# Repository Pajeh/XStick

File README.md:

XStick
======

compact breadboard-friendly XMO XS1-L4 board with USB-UART and all GPIO exposed
.
The board was designed with the freeware version of eagle and the modified design rules of Seeed Studio.
#ToDo list
* solder and test 
* Add at least 2 LEDs on board (soon)

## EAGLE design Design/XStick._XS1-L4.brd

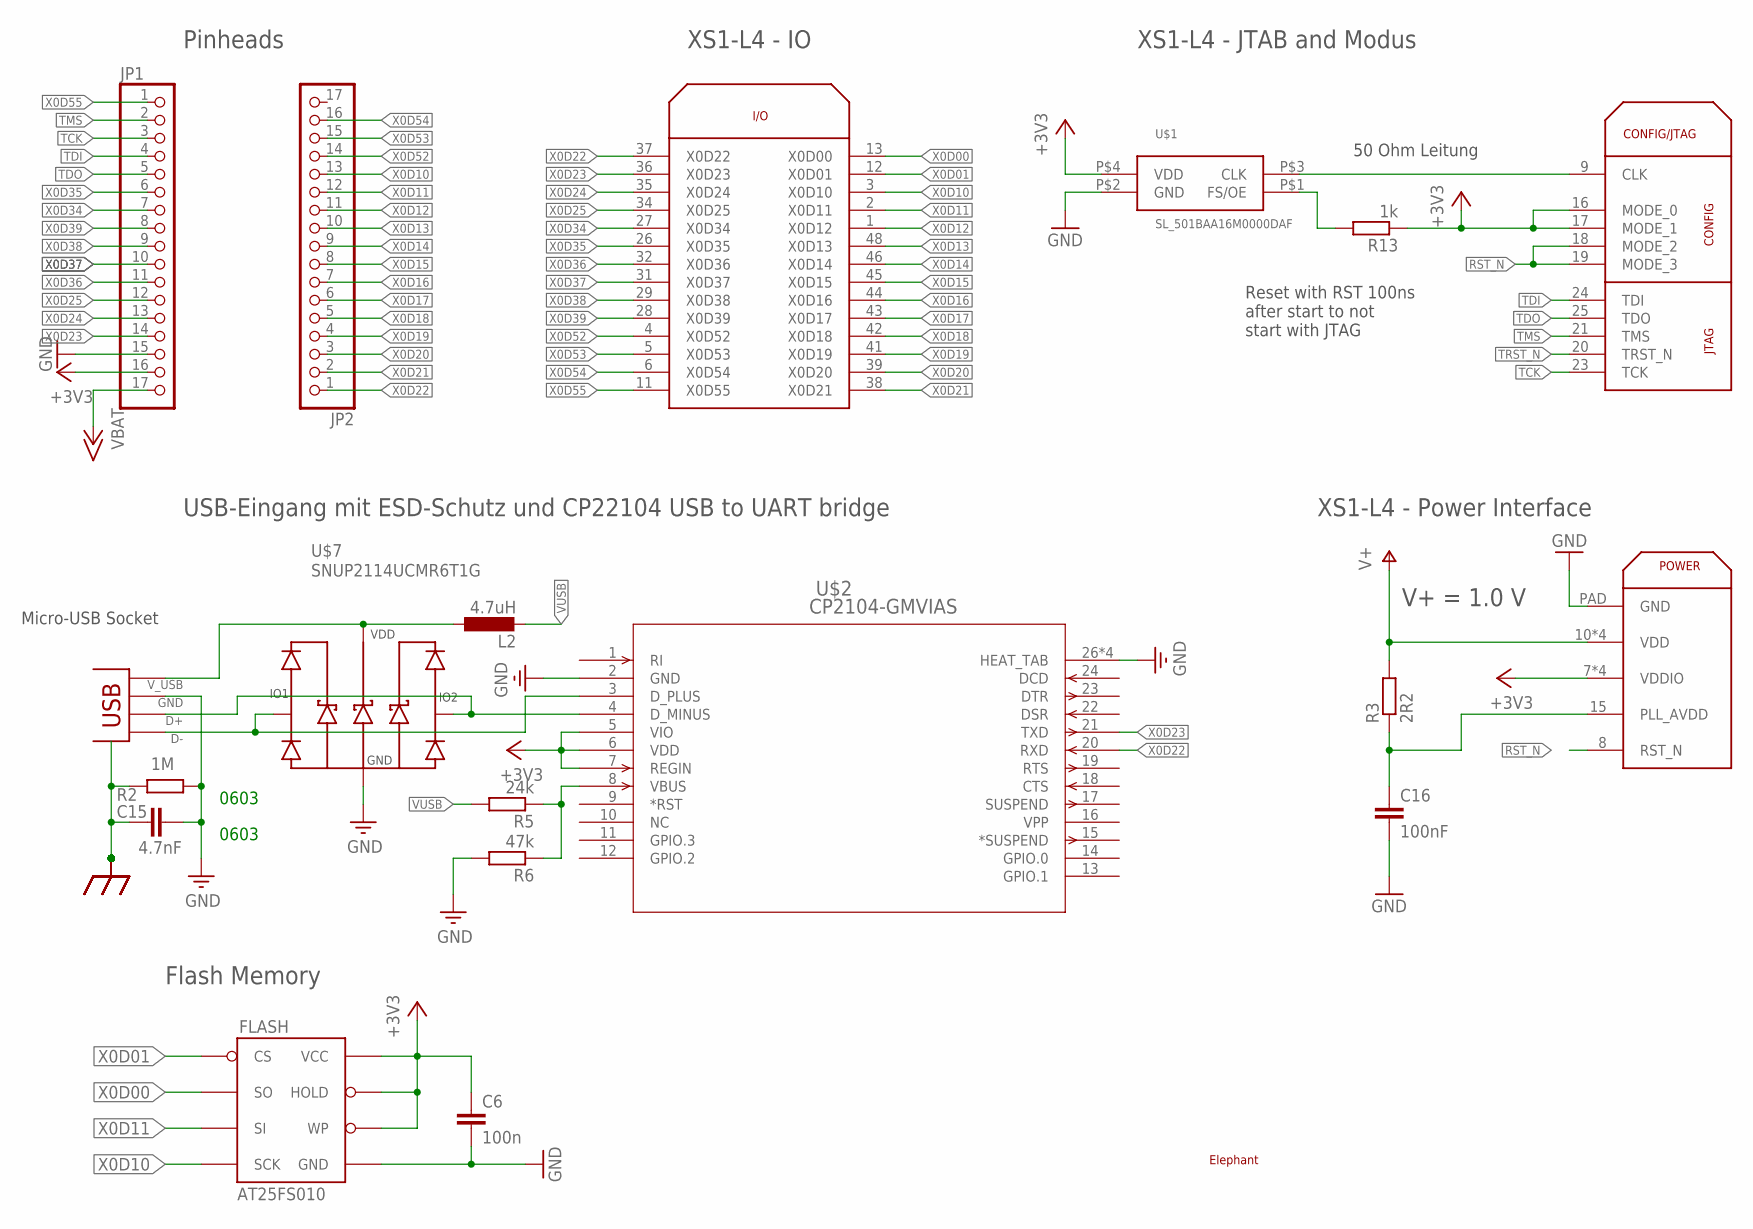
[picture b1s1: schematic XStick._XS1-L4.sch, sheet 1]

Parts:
C6: 100n; C0402
C15: 4.7nF; C0603M
C16: 100nF; C0402
FLASH: AT25FS010; SO08WIDE
JP1, JP2: PINHD-1X17; 1X17
L2: 4.7uH; C0603
R2: 1M; R0603M
R3: 2R2; R0603
R5: 24k; R0603
R6: 47k; R0603
R13: 1k; R0603
U$1: SL_501BAA16M0000DAF; SL_OSZ
U$2: CP2104-GMVIAS; QFN24_4X4_VIAS
U$4: ELEPHANT
U$5: XS1-L01A-TQ48; TQFP48
U$7: SNUP2114UCMR6T1G; TSOP-6
USB_SKT: USB_SHIELD_8; USB_MICRO_B

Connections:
+3V3: C6.1, FLASH.3 (WP), FLASH.7 (HOLD), FLASH.8 (VCC), JP1.16, R13.1, U$1.P$4 (VDD), U$2.5 (VIO), U$2.6 (VDD), U$2.7 (REGIN), U$5.7 (VDDIO), U$5.14 (VDDIO), U$5.16 (MODE_0), U$5.17 (MODE_1), U$5.30 (VDDIO), U$5.40 (VDDIO); also elsewhere on the board
+15V: JP1.17; also elsewhere on the board
D+: U$2.4 (D_MINUS), U$7.1 (I/O1), USB_SKT.D+
D-: U$2.3 (D_PLUS), U$7.6 (I/O2), USB_SKT.D-
GND: C6.2, C15.1, C16.2, FLASH.4 (GND), JP1.15, R2.2, R6.2, U$1.P$2 (GND), U$2.2 (GND), U$2.26 (HEAT_TAB), U$2.27 (HEAT_TAB), U$2.28 (HEAT_TAB), U$2.29 (HEAT_TAB), U$5.PAD (GND), U$7.2 (VN), USB_SKT.GND; also elsewhere on the board
unnamed: U$1.P$3 (CLK), U$5.9 (CLK)
unnamed: L2.1, U$7.5 (VP), USB_SKT.VBUS (V_USB)
unnamed: R13.2, U$1.P$1 (FS/OE)
unnamed: R5.1, R6.1, U$2.8 (VBUS)
unnamed: C16.1, R3.1, U$5.15 (PLL_AVDD)
RST_N: U$5.8 (RST_N), U$5.18 (MODE_2), U$5.19 (MODE_3); also elsewhere on the board
TCK: JP1.3, U$5.23 (TCK)
TDI: JP1.4, U$5.24 (TDI)
TDO: JP1.5, U$5.25 (TDO)
TMS: JP1.2, U$5.21 (TMS)
TRST_N: U$5.20 (TRST_N); also elsewhere on the board
USB_SHIELD: C15.2, R2.1, USB_SKT.SHIELD$1, USB_SKT.SHIELD$2 (SHIELD$1), USB_SKT.SHIELD$3 (SHIELD$1), USB_SKT.SHIELD$4 (SHIELD$1), USB_SKT.SHIELD$5 (SHIELD$1), USB_SKT.SHIELD$6 (SHIELD$1), USB_SKT.SHIELD$7 (SHIELD$1), USB_SKT.SHIELD$8 (SHIELD$1)
V+: R3.2, U$5.10 (VDD), U$5.22 (VDD), U$5.33 (VDD), U$5.47 (VDD); also elsewhere on the board
VUSB: L2.2, R5.2; also elsewhere on the board
X0D00: FLASH.2 (SO), U$5.13 (X0D00)
X0D01: FLASH.1 (CS), U$5.12 (X0D01)
X0D10: FLASH.6 (SCK), JP2.13, U$5.3 (X0D10)
X0D11: FLASH.5 (SI), JP2.12, U$5.2 (X0D11)
X0D12: JP2.11, U$5.1 (X0D12)
X0D13: JP2.10, U$5.48 (X0D13)
X0D14: JP2.9, U$5.46 (X0D14)
X0D15: JP2.8, U$5.45 (X0D15)
X0D16: JP2.7, U$5.44 (X0D16)
X0D17: JP2.6, U$5.43 (X0D17)
X0D18: JP2.5, U$5.42 (X0D18)
X0D19: JP2.4, U$5.41 (X0D19)
X0D20: JP2.3, U$5.39 (X0D20)
X0D21: JP2.2, U$5.38 (X0D21)
X0D22: JP2.1, U$2.20 (RXD), U$5.37 (X0D22)
X0D23: JP1.14, U$2.21 (TXD), U$5.36 (X0D23)
X0D24: JP1.13, U$5.35 (X0D24)
X0D25: JP1.12, U$5.34 (X0D25)
X0D34: JP1.7, U$5.27 (X0D34)
X0D35: JP1.6, U$5.26 (X0D35)
X0D36: JP1.11, U$5.32 (X0D36)
X0D37: JP1.10, U$5.31 (X0D37)
X0D38: JP1.9, U$5.29 (X0D38)
X0D39: JP1.8, U$5.28 (X0D39)
X0D52: JP2.14, U$5.4 (X0D52)
X0D53: JP2.15, U$5.5 (X0D53)
X0D54: JP2.16, U$5.6 (X0D54)
X0D55: JP1.1, U$5.11 (X0D55)

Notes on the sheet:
0603
Micro-USB Socket
50 Ohm Leitung
Reset with RST 100ns after start to not start with JTAG
Pinheads
XS1-L4 - IO
XS1-L4 - JTAB and Modus
XS1-L4 - Power Interface
USB-Eingang mit ESD-Schutz und CP22104 USB to UART bridge
Flash Memory
V+ = 1.0 V

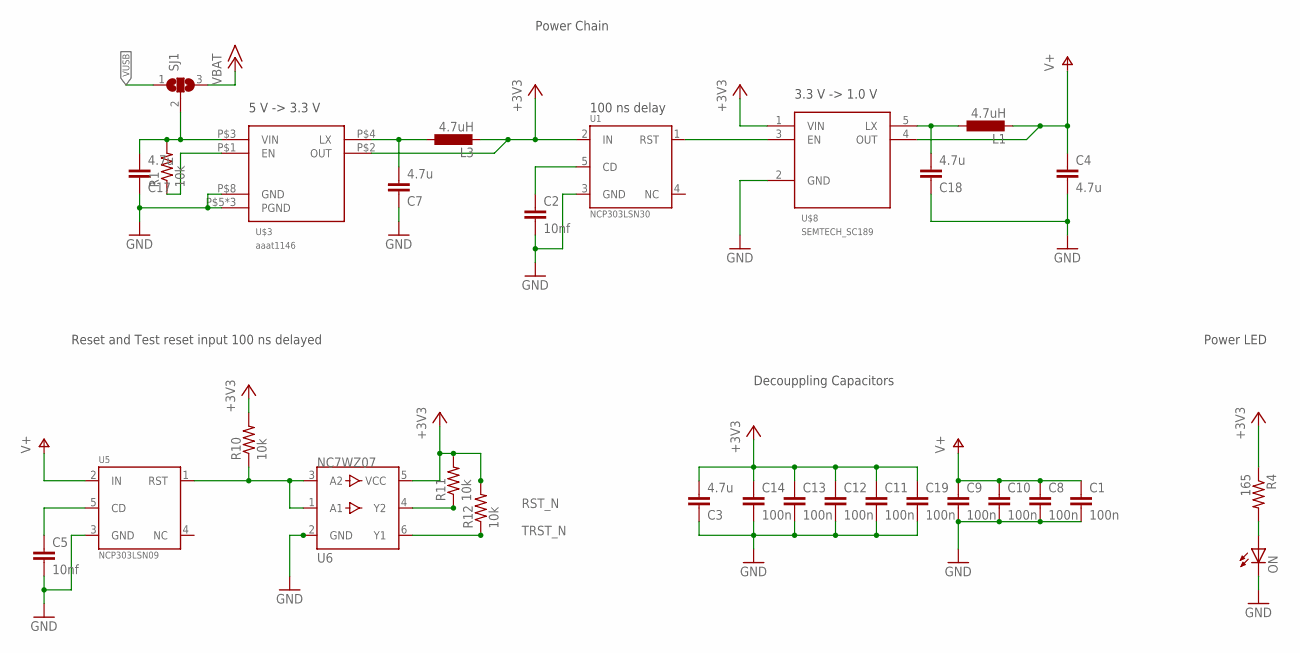
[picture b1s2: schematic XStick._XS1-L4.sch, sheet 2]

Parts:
C1, C8, C9, C10, C11, C12, C13, C14, C19: 100n; C0402
C2, C5: 10nf; 0603-CAP
C3, C4, C7, C17, C18: 4.7u; 0603-CAP
L1, L3: 4.7uH; C0603
ON: LED0603; LED-0603
R1, R10, R11, R12: 10k; 0603-RES
R4: 165; 0603-RES
SJ1: SJ2W; SJ_2
U1: NCP303LSN30; SOT23-5
U5: NCP303LSN09; SOT23-5
U6: NC7WZ07; SC70-6
U$3: aaat1146; SC70JW-8
U$8: SEMTECH_SC189; SOT23-5

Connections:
+3V3: C3.2, C11.1, C12.1, C13.1, C14.1, C19.1, L3.2, R4.1, R10.2, R11.2, R12.2, U1.2 (IN), U6.5 (VCC), U$3.P$2 (OUT), U$8.1 (VIN); also elsewhere on the board
+15V: SJ1.3; also elsewhere on the board
GND: C1.2, C2.2, C3.1, C4.2, C5.2, C7.1, C8.2, C9.2, C10.2, C11.2, C12.2, C13.2, C14.2, C17.1, C18.1, C19.2, ON.C, U1.3 (GND), U5.3 (GND), U6.2 (GND), U$3.P$5 (PGND), U$3.P$6 (PGND), U$3.P$7 (PGND), U$3.P$8 (GND), U$8.2 (GND); also elsewhere on the board
unnamed: C7.2, L3.1, U$3.P$4 (LX)
unnamed: R10.1, U5.1 (RST), U6.1 (A1), U6.3 (A2)
unnamed: ON.A, R4.2
unnamed: C5.1, U5.5 (CD)
unnamed: U1.1 (RST), U$8.3 (EN)
unnamed: C18.2, L1.1, U$8.5 (LX)
unnamed: C2.1, U1.5 (CD)
unnamed: C17.2, R1.2, SJ1.2, U$3.P$3 (VIN)
unnamed: R1.1, U$3.P$1 (EN)
RST_N: R11.1, U6.4 (Y2); also elsewhere on the board
TRST_N: R12.1, U6.6 (Y1); also elsewhere on the board
V+: C1.1, C4.1, C8.1, C9.1, C10.1, L1.2, U5.2 (IN), U$8.4 (OUT); also elsewhere on the board
VUSB: SJ1.1; also elsewhere on the board

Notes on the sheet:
Power Chain
Reset and Test reset input 100 ns delayed
Power LED
Decouppling Capacitors
100 ns delay
3.3 V -> 1.0 V
5 V -> 3.3 V

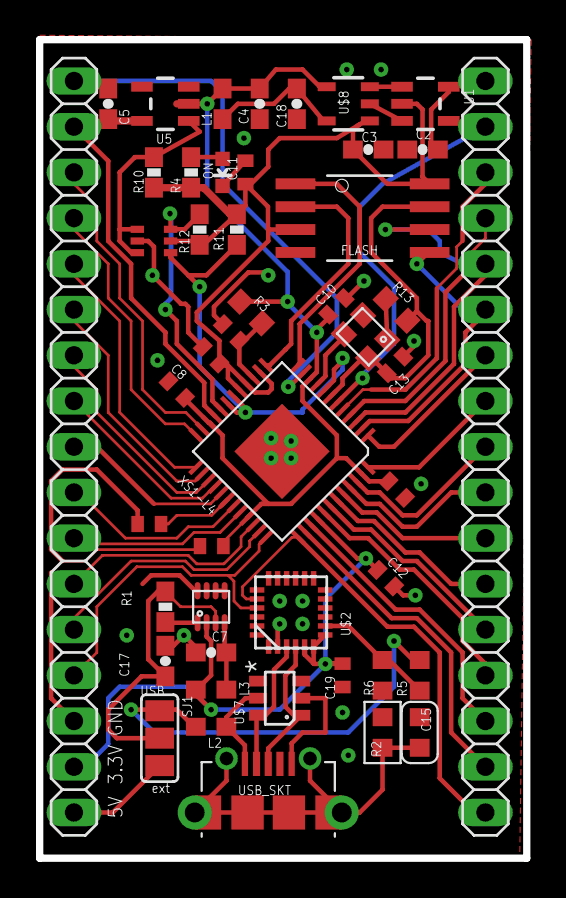
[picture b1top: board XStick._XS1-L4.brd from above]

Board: 2 copper layers, 27.1 x 45.5 mm, 48 parts (1 on the bottom side), 56 nets.

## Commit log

2014-08-11 Save eagle 7.1.0
2014-08-11 only used datasheets
2014-08-11 added ToDo List
